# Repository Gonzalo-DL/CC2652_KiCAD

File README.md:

# CC2652_KiCAD

PCB con TI CC2652R1 con BLE 5.2, con JTAG.

Comunicacion serial via USB conectado a UART y con perifericos:

Led verde: GPIO7

Led rojo: GPIO6

Push button 1: GPIO13

Push button 2: GPIO14

Memoria Flash(W25Q64JWZPIM): (SPI) 

	SCLK: GPIO10
  
	MISO: GPIO8
  
	MOSI: GPIO9
  
	SS: GPIO20

IMU (MPU-6050): (I2C)

	SDA: GPIO24
  
	SCL: GPIO25
  
	FSYNC: GPIO26
  
	Address: 1101000

HALL 3-Axis (TLE493D): (I2C)

	SDA: GPIO24
  
	SCL: GPIO25
  
	Address: (Segun sigla del modelo)
  
		A0: 6AH / 6BH
    
		A1: 44H / 45H
    
		A2: F0H / F1H
    
		A3: 88H / 89H

USB Transceiver (CP2102N): (UART)

	Rx: GPIO19
  
	Tx: GPIO18

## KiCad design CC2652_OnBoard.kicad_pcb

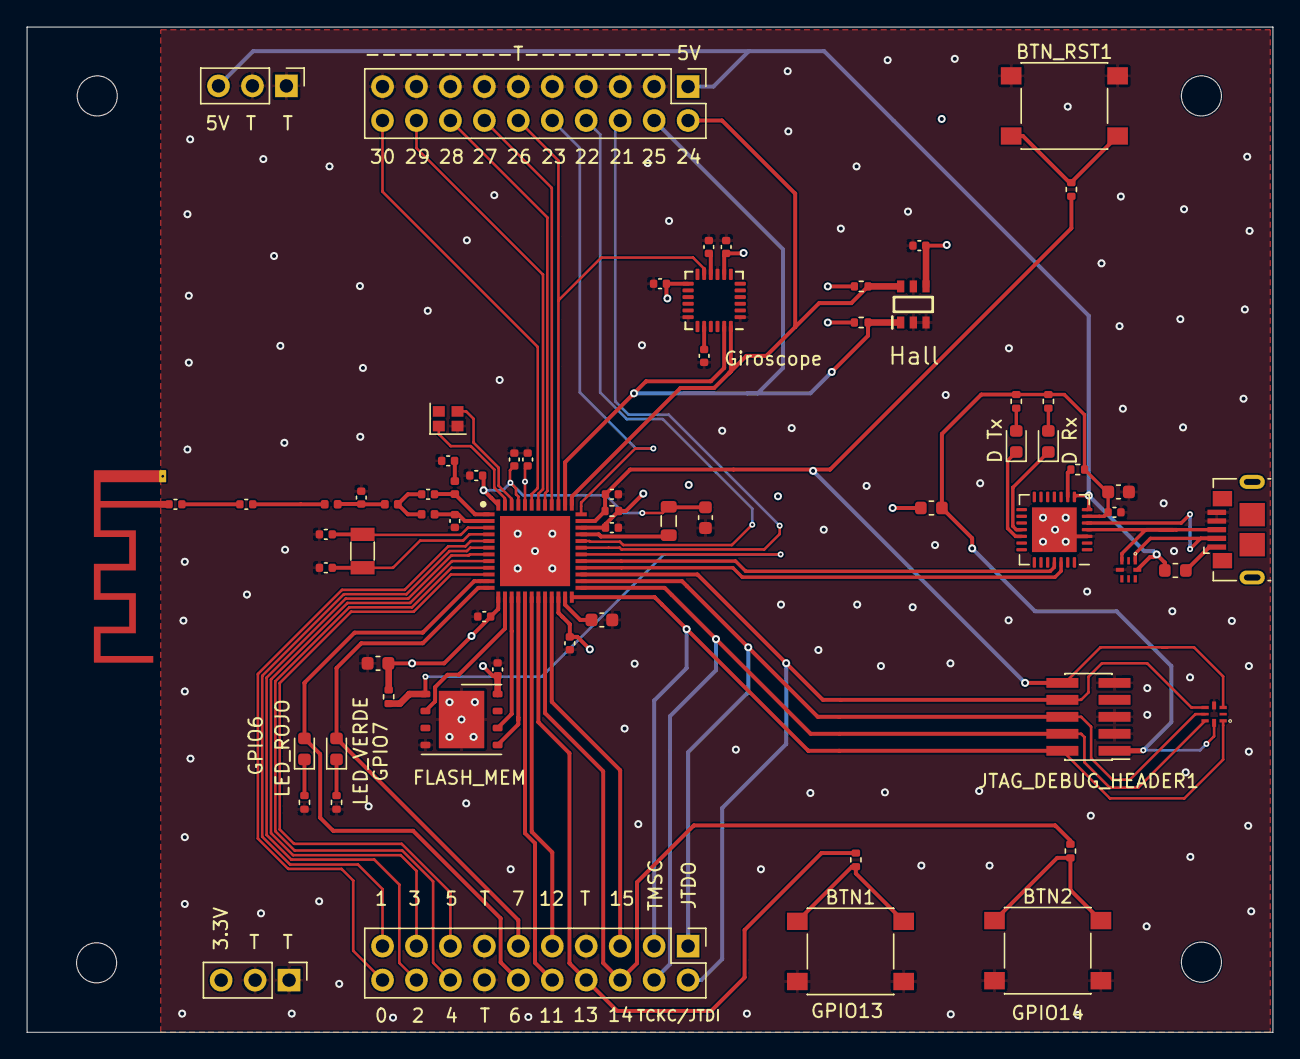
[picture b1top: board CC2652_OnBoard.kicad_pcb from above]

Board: 4 copper layers, 93.2 x 75.2 mm, 67 parts (0 on the bottom side), 67 nets.

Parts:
32KHz_Crystl1: 3215 2 pin; Crystal_SMD_3215-2Pin_3.2x1.5mm
48MHz_Crystal1: CX2016DB48000C0FPLC1; Crystal_SMD_2016-4Pin_2.0x1.6mm
BTN1, BTN2: SW; SW_SPST_PTS645
BTN1_R1, BTN2_R1: 100?; R_0402_1005Metric
BTN_RST1: SW; SW_SPST_PTS645
C1, C2, C303, C305: 12p; C_0402_1005Metric
C3, C102, C103, C104, C105, C106, C107, C108, C109, C111, C112, C204: 0.1u; C_0402_1005Metric
C101: 1u; C_0603_1608Metric
C110: 10n; C_0402_1005Metric
C201, C202: 22u; C_0603_1608Metric
C203: 10u; C_0603_1608Metric
C205: 2.2n; C_0402_1005Metric
C301, C302, C304: 1p; C_0402_1005Metric
C306: 1.8p; C_0402_1005Metric
CP2102_nRST_R1: 10k; R_0402_1005Metric
D Rx: rojo; LED_0603_1608Metric
D Tx: VERDE; LED_0603_1608Metric
EMI_VDDS_FILTER1: BLM18HE152SN1D; L_0603_1608Metric
EMI_VDDS_FILTER_USB1: BLM18HE152SN1D; L_0603_1608Metric
FLASH_MEM: W25Q64JWZPIM; WSON-8-1EP_6x5mm_P1.27mm_EP3.4x4.3mm
FLASH_nCS_PUR1: 2.2k; R_0402_1005Metric
Giroscope: MPU-6050(I2C); InvenSense_QFN-24_4x4mm_P0.5mm
HALL_SCL_PUR1: 1k; R_0402_1005Metric
HALL_SDA_PUR1: 1k; R_0402_1005Metric
Hall: TLE493DW2B6A2HTSA1; SOT95P280X110-6N
IC1: CC2652R1FRGZR; QFN50P700X700X100-49N-D
JTAG_DEBUG_HEADER1: FTSH-105-01; PinHeader_2x05_P1.27mm_Vertical_SMD
JTAG_ESD1: TPD6E004RSER; RSE0008A
L31, L32: 2.4n; L_0402_1005Metric
L33, L34: 2n; L_0402_1005Metric
L101: 6.8u; L_0805_2012Metric
LED_ROJO: LED; LED_0603_1608Metric
LED_VERDE: LED; LED_0603_1608Metric
PINS_DER1: Conn_02x10_Odd_Even; PinHeader_2x10_P2.54mm_Vertical
PINS_IZQ1: Conn_02x10_Odd_Even; PinHeader_2x10_P2.54mm_Vertical
PINS_PWR_DER1: Conn_01x03; PinHeader_1x03_P2.54mm_Vertical
PINS_PWR_IZQ1: Conn_01x03; PinHeader_1x03_P2.54mm_Vertical
R3: 100k; R_0402_1005Metric
R_LED_ROJO1: 180; R_0402_1005Metric
R_LED_USB_Rx1: 180; R_0402_1005Metric
R_LED_USB_Tx1: 220; R_0402_1005Metric
R_LED_VERDE1: 220; R_0402_1005Metric
R_RESET1: 100; R_0402_1005Metric
USB_CONNECTOR_A1: U217-041N-4BV81; USB_Micro-B_GCT_USB3076-30-A
USB_ESD1: TPD6E004RSER; RSE0008A
USB_UART1: CP2102N-A01-GQFN28; QFN-28-1EP_5x5mm_P0.5mm_EP3.35x3.35mm

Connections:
CP2102_RX: IC1.29, USB_UART1.25
CP2102_RX_LED: D Rx.1, USB_UART1.18
CP2102_TX: IC1.28, USB_UART1.26
CP2102_TX_LED: D Tx.1, USB_UART1.19
CP2102_nRST: CP2102_nRST_R1.2, USB_UART1.9
DCDC_OUT: IC1.33, L101.1
FLASH_CLK: FLASH_MEM.6, IC1.15
FLASH_SDI: FLASH_MEM.5, IC1.16
FLASH_SDO: FLASH_MEM.2, IC1.14
FLASH_nCS: FLASH_MEM.1, FLASH_nCS_PUR1.2, IC1.30
GND: 48MHz_Crystal1.2, BTN1.2, BTN2.2, BTN_RST1.1, C1.1, C2.1, C3.2, C101.2, C102.1, C103.1, C104.1, C105.1, C106.1, C107.1, C108.2, C109.1, C110.2, C111.1, C112.1, C201.1, C202.1, C203.2, C204.2, C205.1, C301.2, C303.1, C304.2, FLASH_MEM.4, FLASH_MEM.9, Giroscope.1, Giroscope.9, Giroscope.18, Hall.2, Hall.3, Hall.5, IC1.49, JTAG_DEBUG_HEADER1.3, JTAG_DEBUG_HEADER1.5, JTAG_DEBUG_HEADER1.9, JTAG_ESD1.4, PINS_DER1.7, PINS_DER1.13, PINS_DER1.14, PINS_IZQ1.3, PINS_IZQ1.5, PINS_IZQ1.7, PINS_IZQ1.9, PINS_IZQ1.11, PINS_IZQ1.13, PINS_IZQ1.15, PINS_IZQ1.17, PINS_IZQ1.19, PINS_PWR_DER1.1, PINS_PWR_DER1.2, PINS_PWR_IZQ1.1, PINS_PWR_IZQ1.2, R_LED_ROJO1.2, R_LED_VERDE1.2, USB_CONNECTOR_A1.4, USB_CONNECTOR_A1.5, USB_ESD1.4, USB_UART1.3, USB_UART1.29
GPIO0: IC1.5, PINS_DER1.20
GPIO1: IC1.6, PINS_DER1.19
GPIO2: IC1.7, PINS_DER1.18
GPIO3: IC1.8, PINS_DER1.17
GPIO4: IC1.9, PINS_DER1.16
GPIO5: IC1.10, PINS_DER1.15
GPIO6: IC1.11, LED_ROJO.2, PINS_DER1.12
GPIO7: IC1.12, LED_VERDE.2, PINS_DER1.11
GPIO11: IC1.17, PINS_DER1.10
GPIO12: IC1.18, PINS_DER1.9
GPIO13: BTN1_R1.1, IC1.19, PINS_DER1.8
GPIO14: BTN2_R1.1, IC1.20, PINS_DER1.6
GPIO15: IC1.21, PINS_DER1.5
GPIO16-JTDO: IC1.26, JTAG_DEBUG_HEADER1.6, JTAG_ESD1.6, PINS_DER1.1
GPIO17-JTDI: IC1.27, JTAG_DEBUG_HEADER1.8, JTAG_ESD1.5, PINS_DER1.2
GPIO21: IC1.31, PINS_IZQ1.6
GPIO22: IC1.32, PINS_IZQ1.8
GPIO23: IC1.36, PINS_IZQ1.10
GPIO24: Giroscope.24, HALL_SDA_PUR1.2, Hall.6, IC1.37, PINS_IZQ1.2
GPIO25: Giroscope.23, HALL_SCL_PUR1.2, Hall.1, IC1.38, PINS_IZQ1.4
GPIO26: Giroscope.11, IC1.39, PINS_IZQ1.12
GPIO27: IC1.40, PINS_IZQ1.14
GPIO28: IC1.41, PINS_IZQ1.16
GPIO29: IC1.42, PINS_IZQ1.18
GPIO30: IC1.43, PINS_IZQ1.20
JTAG_TCKC: IC1.25, JTAG_DEBUG_HEADER1.4, JTAG_ESD1.7, PINS_DER1.4
JTAG_TMSC: IC1.24, JTAG_DEBUG_HEADER1.2, JTAG_ESD1.1, PINS_DER1.3
unnamed: BTN1.1, BTN1_R1.2
unnamed: BTN2.1, BTN2_R1.2
unnamed: BTN_RST1.2, R_RESET1.2
unnamed: C101.1, IC1.23
unnamed: C204.1, Giroscope.10
unnamed: C205.2, Giroscope.20
unnamed: C302.1, L31.2, L33.1
unnamed: C303.2, L32.1
unnamed: C304.1, L33.2, L34.1
unnamed: C305.1, C306.2
unnamed: C305.2, L34.2
unnamed: D Rx.2, R_LED_USB_Rx1.2
unnamed: D Tx.2, R_LED_USB_Tx1.2
unnamed: EMI_VDDS_FILTER_USB1.2, USB_CONNECTOR_A1.1
unnamed: LED_ROJO.1, R_LED_ROJO1.1
unnamed: LED_VERDE.1, R_LED_VERDE1.1
RESET_N: C3.1, IC1.35, JTAG_DEBUG_HEADER1.10, JTAG_ESD1.3, R3.2, R_RESET1.1
RF_N: C301.1, IC1.2, L31.1
RF_P: C302.2, IC1.1, L32.2
USB_D+: USB_CONNECTOR_A1.3, USB_ESD1.3, USB_UART1.4
USB_D-: USB_CONNECTOR_A1.2, USB_ESD1.1, USB_UART1.5
USB_VBUS: EMI_VDDS_FILTER_USB1.1, PINS_IZQ1.1, PINS_PWR_IZQ1.3, USB_ESD1.8, USB_UART1.7, USB_UART1.8
VDDR: C106.2, C107.2, C202.2, IC1.45, IC1.48, L101.2
VDDS: C102.2, C103.2, C104.2, C105.2, C109.2, C110.1, C111.2, C112.2, C201.2, EMI_VDDS_FILTER1.1, FLASH_MEM.8, FLASH_nCS_PUR1.1, Giroscope.8, Giroscope.13, HALL_SCL_PUR1.1, HALL_SDA_PUR1.1, Hall.4, IC1.13, IC1.22, IC1.34, IC1.44, PINS_PWR_DER1.3, R3.1
Vin_CC2652: C108.1, C203.1, CP2102_nRST_R1.1, EMI_VDDS_FILTER1.2, JTAG_DEBUG_HEADER1.1, JTAG_ESD1.8, R_LED_USB_Rx1.1, R_LED_USB_Tx1.1, USB_UART1.6
X32K_Q1: 32KHz_Crystl1.1, C1.2, IC1.3
X32K_Q2: 32KHz_Crystl1.2, C2.2, IC1.4
X48M_N: 48MHz_Crystal1.3, IC1.46
X48M_P: 48MHz_Crystal1.1, IC1.47

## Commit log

2021-08-11 Update PINS
2021-08-18 Update+UL PCB
2021-08-18 Add rar
2021-08-18 3d View
2021-08-26 V2 PIN Route
2021-09-02 Agregar PNGS
2021-09-13 footprints
